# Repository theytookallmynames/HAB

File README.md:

# HAB
High altitude balloon project for Bergen's 2018 STEM program

## Setting up your development environment

1. Clone this repo.
2. Install the Arduino IDE: https://www.arduino.cc/en/main/software
3. Open the `HAB` directory in the repo in the IDE
4. Follow [these instructions](https://learn.adafruit.com/adafruit-feather-32u4-basic-proto/arduino-ide-setup) to install the "Adafruit AVR Boards" package in the IDE, and then set the board for the sketch to "Adafruit Feather M0" under the Tools > Boards menu.

You may need to install some additional libraries. To do that, go to the Tools menu in the Arduino IDE, search for the missing libraries, and hit the install button.

## Building the code

In the Arduino IDE, hit the checkmark button at the top of the window (or select Verify/Compile in the Sketch menu). This will make sure the code compiles correctly and will give some information at the bottom of the screen such as how much storage the compiled binary will take up on the device, and how much dynamic memory will be available for the program after global variables are taken into account.

## Installing on the arduino

In the Arduino IDE, press the button with the arrow (next to the button with the checkmark). If the code verifies properly, it will get uploaded to the Arduino and the Arduino will restart with the new code.

## Hardware

See the docs folder for datasheets.

### Board

Adafruit Feather M0 Adalogger

https://learn.adafruit.com/adafruit-feather-m0-adalogger/overview

### Sensors

#### Temperature sensor

Velleman VMA320 analog temperature sensor module

#### Pressure sensor

Honeywell HSCRNN1.6BA2A3

#### GPS receiver

Byonics GPS5HAOEM module
NaviSys GM-401 SiRFstarIV chip

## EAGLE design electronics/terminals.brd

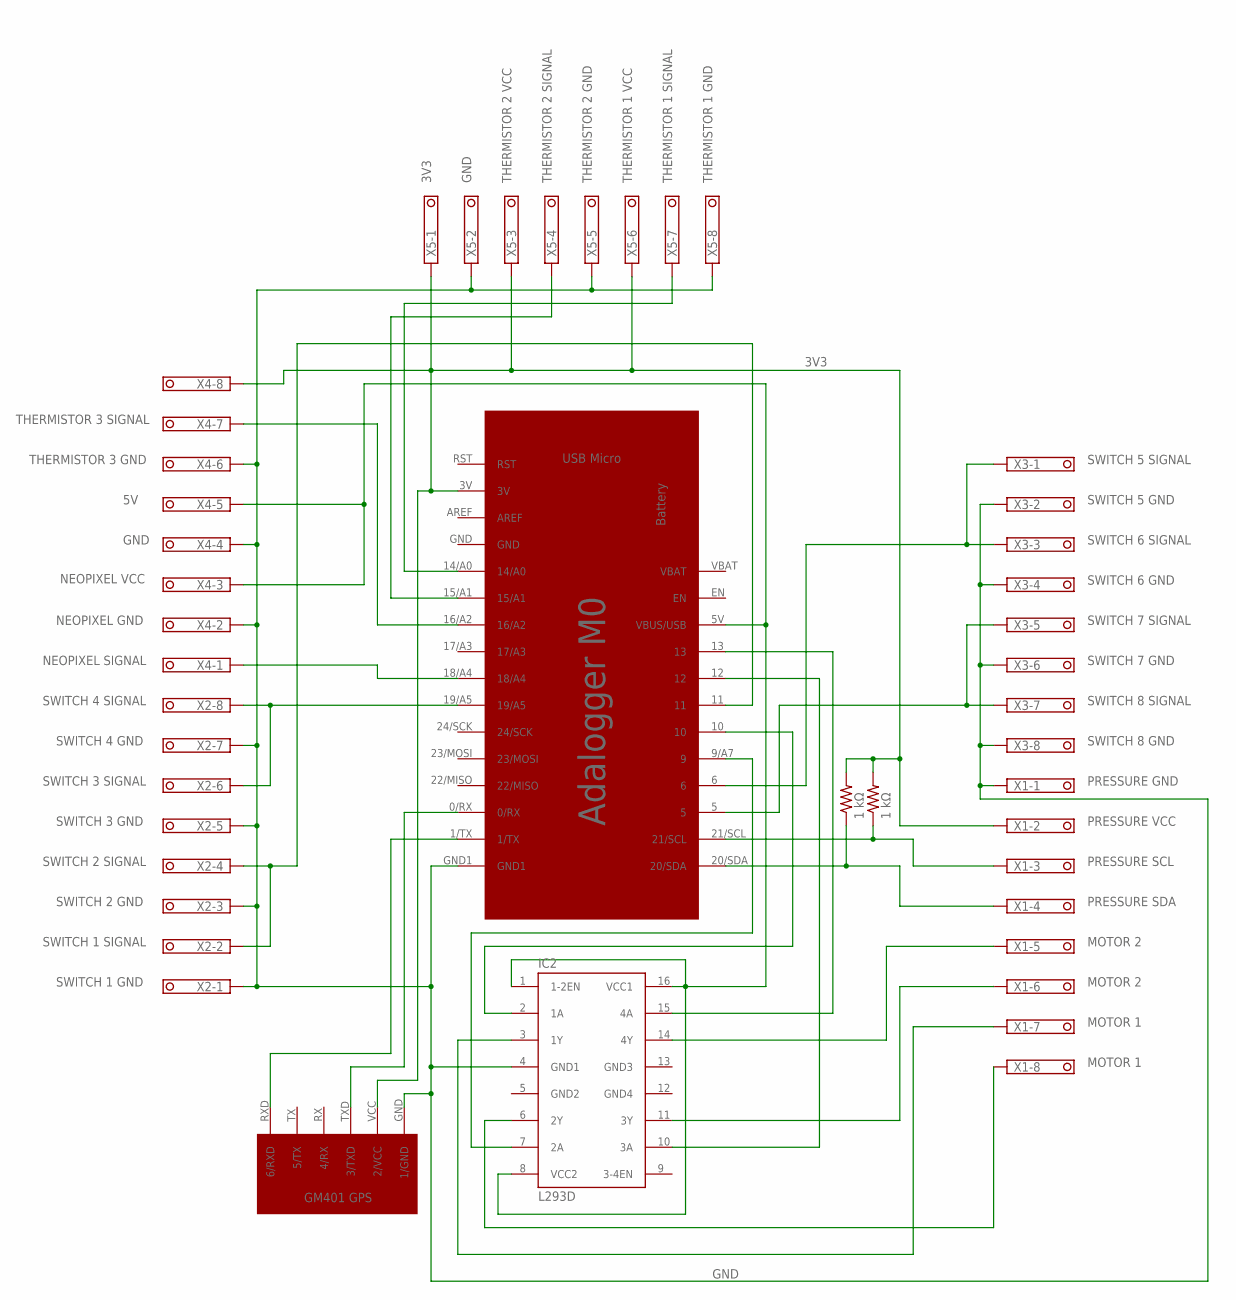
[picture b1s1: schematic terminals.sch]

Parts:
IC2: L293D; DIL16
M0: Adalogger M0; BOARD
R1, R5: 1 kΩ; 0204V
U$1: GPS; GPS_BREAKOUT
X1, X2, X3, X4, X5: 1751303

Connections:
3V3: M0.3V, R1.2, R5.2, U$1.VCC (2/VCC), X1.2, X4.8, X5.1, X5.3, X5.6
5V: IC2.1 (1-2EN), IC2.8 (VCC2), IC2.16 (VCC1), M0.5V (VBUS/USB), X4.3, X4.5
GND: IC2.4 (GND1), M0.GND1, U$1.GND (1/GND), X1.1, X2.1, X2.3, X2.5, X2.7, X3.2, X3.4, X3.6, X3.8, X4.2, X4.4, X4.6, X5.2, X5.5, X5.8
GND2: IC2.5 (GND2)
GND3: IC2.13 (GND3)
GND4: IC2.12 (GND4)
GPS_RX: M0.1/TX, U$1.RXD (6/RXD)
GPS_TX: M0.0/RX, U$1.TXD (3/TXD)
L293_1A: IC2.2 (1A), M0.10
L293_2A: IC2.7 (2A), M0.9/A7 (9)
MOTOR_1_NEG: IC2.6 (2Y), X1.8
MOTOR_1_POS: IC2.3 (1Y), X1.7
MOTOR_2_NEG: IC2.11 (3Y), X1.6
MOTOR_2_POS: IC2.14 (4Y), X1.5
unnamed: IC2.15 (4A), M0.13
unnamed: IC2.10 (3A), M0.12
NEOPIXEL_SIG: M0.18/A4, X4.1
SCL: M0.21/SCL, R5.1, X1.3
SDA: M0.20/SDA, R1.1, X1.4
SW_1_2_SIG: M0.11, X2.2, X2.4
SW_3_4_SIG: M0.19/A5, X2.6, X2.8
SW_5_6_SIG: M0.6, X3.1, X3.3
SW_7_8_SIG: M0.5, X3.5, X3.7
THERM_1_SIG: M0.14/A0, X5.7
THERM_2_SIG: M0.15/A1, X5.4
THERM_3_SIG: M0.16/A2, X4.7

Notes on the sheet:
MOTOR 2
MOTOR 1
PRESSURE SDA
PRESSURE SCL
PRESSURE VCC
SWITCH 8 GND
SWITCH 8 SIGNAL
PRESSURE GND
SWITCH 7 GND
SWITCH 1 GND
SWITCH 1 SIGNAL
SWITCH 2 GND
SWITCH 3 SIGNAL
SWITCH 3 GND
SWITCH 2 SIGNAL
SWITCH 4 GND
SWITCH 4 SIGNAL
NEOPIXEL SIGNAL
NEOPIXEL GND
NEOPIXEL VCC
GND
THERMISTOR 3 GND
3V3
THERMISTOR 2 VCC
THERMISTOR 2 SIGNAL
THERMISTOR 2 GND
THERMISTOR 1 VCC
THERMISTOR 1 SIGNAL
THERMISTOR 1 GND
SWITCH 7 SIGNAL
SWITCH 6 GND
SWITCH 6 SIGNAL
SWITCH 5 GND
SWITCH 5 SIGNAL
THERMISTOR 3 SIGNAL

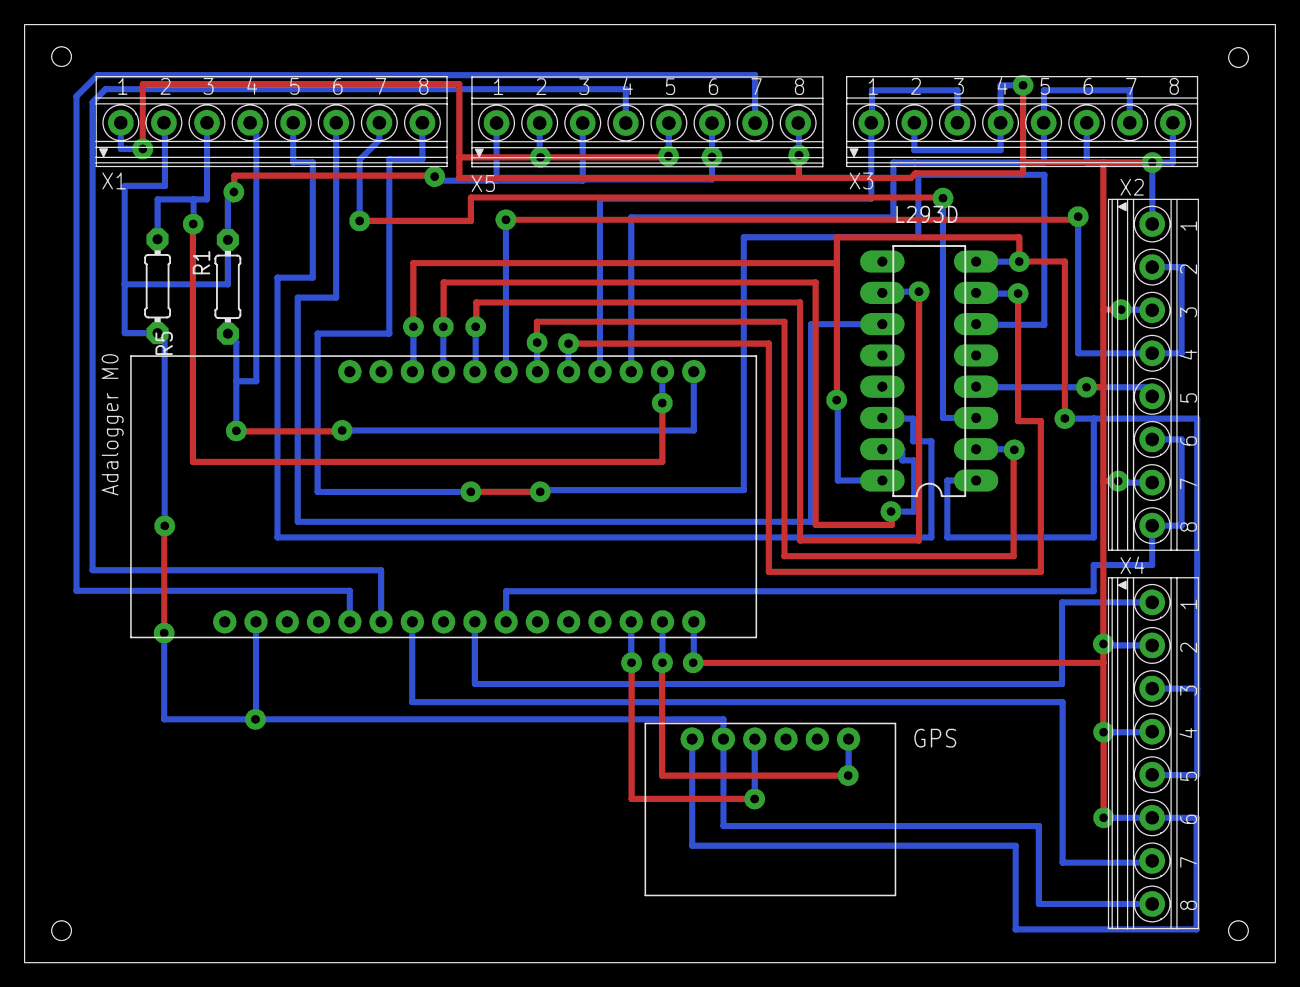
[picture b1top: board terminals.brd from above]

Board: 2 copper layers, 101.6 x 76.2 mm, 10 parts (0 on the bottom side), 23 nets.

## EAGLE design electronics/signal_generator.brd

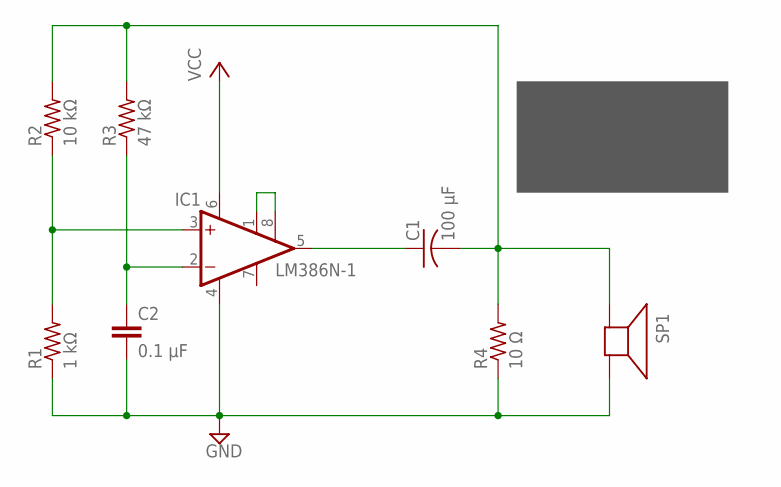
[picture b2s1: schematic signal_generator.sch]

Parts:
C1: 100 µF; C025-024X044
C2: 0.1 µF; C2.5-3
IC1: LM386N-1; DIL08
R1: 1 kΩ; 0204/7
R2: 10 kΩ; 0204/7
R3: 47 kΩ; 0204/7
R4: 10 Ω; 0204/7
SP1: SPEAKER/AL60P; AL60P

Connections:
GND: C2.2, IC1.4 (GND), R1.1, R4.1, SP1.2 (-)
OUT: C1.2, R2.2, R3.2, R4.2, SP1.1 (+)
PIN1-8: IC1.1 (GAIN), IC1.8 (GAIN)
PIN2: C2.1, IC1.2 (-IN), R3.1
PIN3: IC1.3 (+IN), R1.2, R2.1
PIN5: C1.1, IC1.5 (OUT)
VCC: IC1.6 (VS)

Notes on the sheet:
BCC HAB Signal Generator Version 1.0 06/04/2019

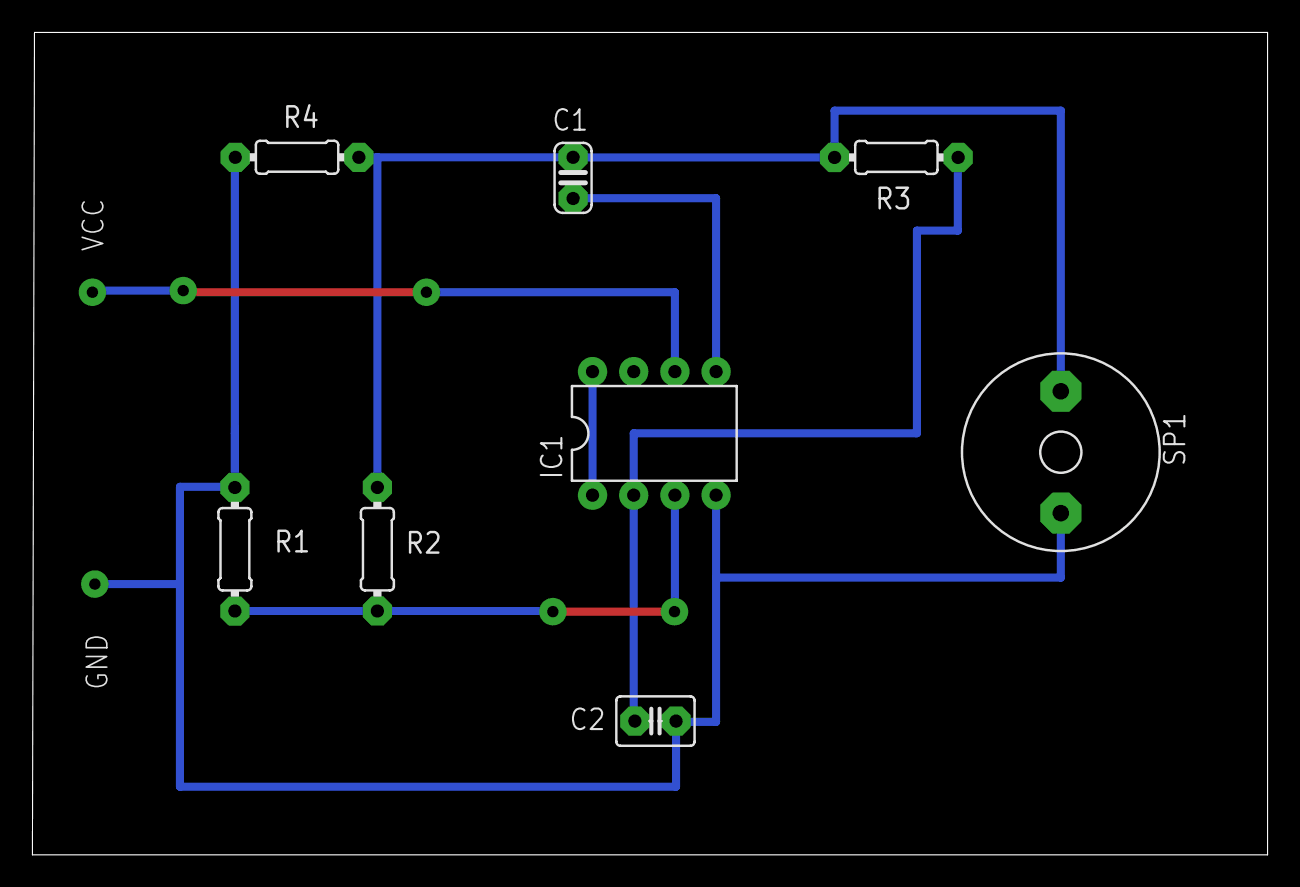
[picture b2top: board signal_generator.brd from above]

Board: 2 copper layers, 76.2 x 50.7 mm, 8 parts (0 on the bottom side), 6 nets.

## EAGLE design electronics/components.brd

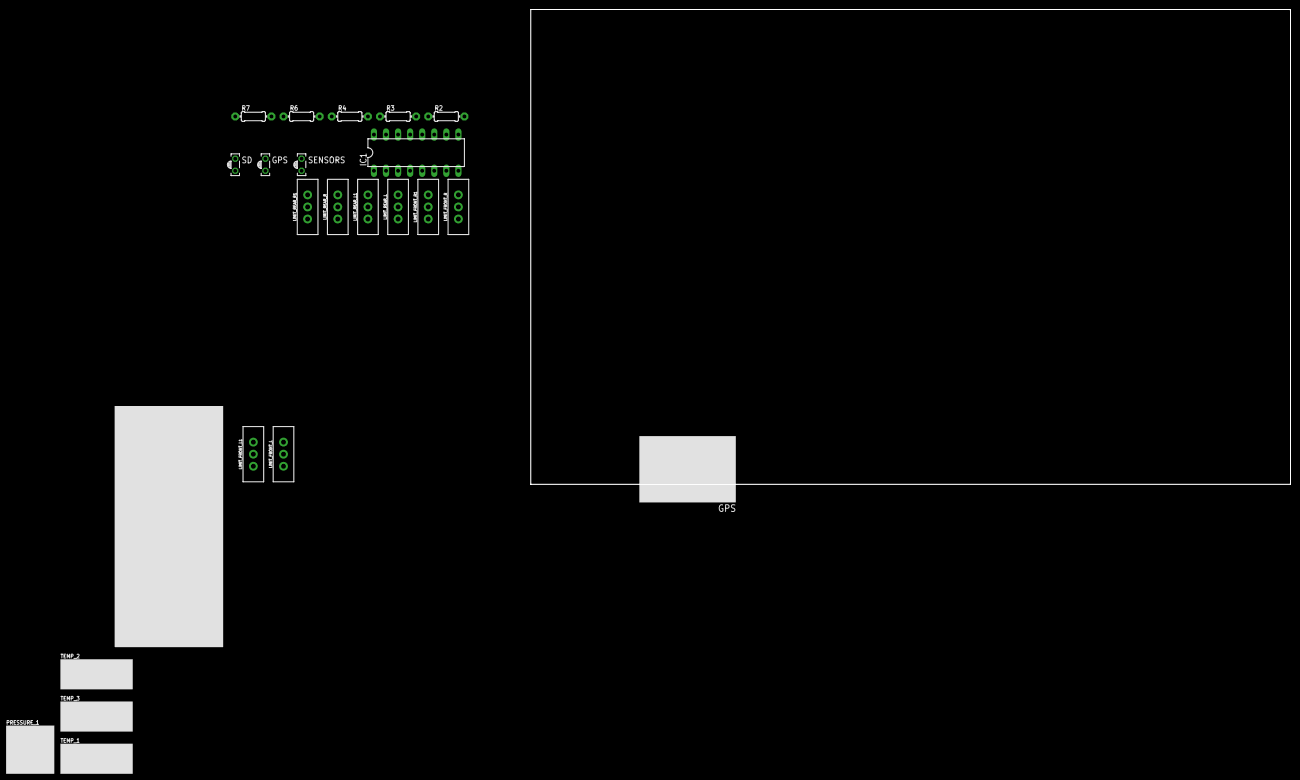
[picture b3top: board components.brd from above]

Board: 2 copper layers, 160.0 x 100.0 mm, 23 parts (0 on the bottom side), 26 nets, no tracks yet.

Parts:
GPS: IRL80A
IC1: L293D; DIL16
LIMIT_FRONT_L, LIMIT_FRONT_L1: SWITCH_SPDT_PTH_11.6X4.0MM
LIMIT_FRONT_R, LIMIT_FRONT_R1: SWITCH_SPDT_PTH_11.6X4.0MM
LIMIT_REAR_L, LIMIT_REAR_L1: SWITCH_SPDT_PTH_11.6X4.0MM
LIMIT_REAR_R, LIMIT_REAR_R1: SWITCH_SPDT_PTH_11.6X4.0MM
PRESSURE_1: PRESSURE; HSC_PRESSURE
R2, R3, R4: 4k7 Ω; 0204/7
R6, R7: 1 kΩ; 0204/7
SD: IRL80A
SENSORS: IRL80A
TEMP_1, TEMP_2, TEMP_3: VMA320
U$1: ADALOGGER_M0; BOARD
U$3: GPS; GPS_BREAKOUT

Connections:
3.3V: PRESSURE_1.VCC, R6.1, R7.1, TEMP_1.VCC, TEMP_2.VCC, TEMP_3.VCC, U$1.3V, U$3.VCC
5V: IC1.1, IC1.8, IC1.16, U$1.5V
GND: IC1.5, LIMIT_FRONT_L.3, LIMIT_FRONT_L1.3, LIMIT_FRONT_R.3, LIMIT_FRONT_R1.3, LIMIT_REAR_L.3, LIMIT_REAR_L1.3, LIMIT_REAR_R.3, LIMIT_REAR_R1.3, PRESSURE_1.GND, U$1.GND1, U$3.GND
unnamed: TEMP_1.GND, TEMP_2.GND, TEMP_3.GND, U$1.GND
unnamed: U$1.0/RX, U$3.TXD
unnamed: TEMP_2.S, U$1.14/A0
unnamed: U$1.1/TX, U$3.RXD
unnamed: IC1.2, U$1.10
unnamed: PRESSURE_1.SDA, R6.2, U$1.20/SDA
unnamed: PRESSURE_1.SCL, R7.2, U$1.21/SCL
unnamed: TEMP_1.S, U$1.16/A2
unnamed: R4.2, SENSORS.A
unnamed: GPS.A, R3.2
unnamed: R2.2, SD.A
unnamed: IC1.7, U$1.9/A7
unnamed: LIMIT_REAR_L.2, LIMIT_REAR_R.2, U$1.5
unnamed: TEMP_3.S, U$1.15/A1
unnamed: IC1.10, U$1.12
unnamed: GPS.K, SD.K, SENSORS.K
unnamed: IC1.15, U$1.13
unnamed: LIMIT_FRONT_L1.2, LIMIT_FRONT_R1.2, U$1.11
unnamed: R4.1, U$1.22/MISO
unnamed: LIMIT_REAR_L1.2, LIMIT_REAR_R1.2, U$1.19/A5
unnamed: LIMIT_FRONT_L.2, LIMIT_FRONT_R.2, U$1.6
unnamed: R3.1, U$1.23/MOSI
unnamed: R2.1, U$1.24/SCK

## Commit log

2018-08-09 Final???
2018-08-09 Lisence fix
2018-08-09 open and close
2018-08-09 Temp
2018-08-15 motor tests pins
2018-08-16 Mapping needs to be implemented
2018-08-16 temprature sensor and motors
2019-02-20 add documentation and clearer variable names
2019-02-22 add missing datasheets
2019-02-22 add hardware info to README
2019-02-23 write entire GPS line to disk instead of parsing
    Previously the GPS data was parsed into a struct and only certain fields
    were written to the log file. There's no reason to do this while the
    balloon is in the air, so instead just write the entire line to disk and
    then it can be parsed later.
    Also, slight refactor with constants moved to a header file and all
    project source files moved to the HAB directory.
2019-04-28 rewrite for better organization and new board and sensors
2019-05-03 add pin definitions for second payload
2019-05-20 Added Thermistor class
2019-05-20 Added thermistor pins
2019-05-20 Added temperature logging
2019-05-20 Removed temperature related code from Sensors
2019-05-28 - Removed Thermistor declaring/defining from HAB file and moved to Sensors. - Added pre-flight temperature sensors check. - All three thermistors work properly.
2019-06-03 Implemented open and close logic for both doors
2019-06-05 Removed blinking LED code from GPS file
2019-06-10 Logging Module Updates:
    - Created a MissionData class that creates .csv and titles.
    - Added Initialization check for created MissionData & SystemData files.
    - Updated the name of logged files with accordance to restrictions of characters
    - Updated Logging in main HAB file
2019-06-12 Logging module updates:
    - Created separate methods for setting mission data values.
    - Added reading and closing the file for pre-flight check.
    -- Door logic in main loop is created but needs work.
2019-06-13 Logging module updates and clean up:
    - Switched missionFile.read() to systemFile.read() in Logging.
    - Removed commented out old logic.
2019-06-13 Pins update:
    - changed pins for LEDs and Temperature sensors
2019-06-19 Cleaned up Logging & Door opening:
    - removed old comments and debug messages
    - adjusted door opening/closing altitude in main header file
    - removed door status check from adjustDoorIfNeeded
2019-06-19 Door opening logic clean up: - removed lines associated with door status check
2019-06-19 Removed GPS LEDs blinking
2019-06-20 Removed two lines with capital letters HAB_Logging.h
2019-06-20 Temp sensors, LEDs and switches pins update
2019-06-25 Initialize the door in the main loop Added in the Intermediate state to enum DoorStatus Fixed open and close door logic
2019-06-26 Created the HAB_LED.ino and HAB_LED.h files that uses the neopixel LED strip and replaces the three status LEDs we had.
2019-06-26 Removed the reference to DOOR_SPEED and reverted the GPS timeout to 60000 ms.
2019-06-27 Changed the value pending to get a better yellow.
2019-06-27 Added a comment explaining how the values for the Colors enum were determined.
2019-07-01 minor cleanup and formatting fixes
2019-07-04 Logging and GPS changes:
    - Logging mission and system info logic is completed
    - Switched to NeoGPS library for getting GPS information
2019-07-08 Add eagle schematic files to repo
2019-07-22 Logging Update
    - Updated logging procedure to not depend on GPS
    - Added milliseconds as a main timestamp
    - Successfully tested - logging of data continued with the loss of GPS signal
2019-07-22 Formatting changes in logging
2019-07-22 Dents
2019-07-24 Changed the pressure min output and pressure max output for more accurate pressure data.
2019-07-24 Added comment explaining pressure value changes.
2019-07-30 Fixed issue where the serial monitor was outputting that the doors were opened after they timed out.
2019-07-30 Add additional vias to the board layout
    Any traces that need to connect to the pins of an IC (arduino, GPS or
    motor driver) need to do so on the bottom layer. So any traces
    that are on the top layer need to be routed through a via to the
    bottom layer.
2019-07-30 increase size of routes and pads
2019-08-06 move all traces except vias to bottom layer
2019-08-07 Edited the code so that the status LED for the GPS will change to a failure state if the GPS loses a signal after 60 seconds.
2019-08-13 update GPS status LED after initialization
2019-08-14 log full NMEA sentences
2019-08-15 Fixed pull request from vitosamson HAB repository for personal repository.
2020-06-30 Added the latest schematic and added the schematic for the tone generator to the docs file.
2024-06-24 Adafruit Grand Central Pinout
2024-07-22 Add files via upload
    Copy of the Schematic from 2023 Summer.

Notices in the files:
parts and their libraries:
SparkFun-Switches: Licensing: Creative Commons ShareAlike 4.0 International - https://creativecommons.org/licenses/by-sa/4.0
